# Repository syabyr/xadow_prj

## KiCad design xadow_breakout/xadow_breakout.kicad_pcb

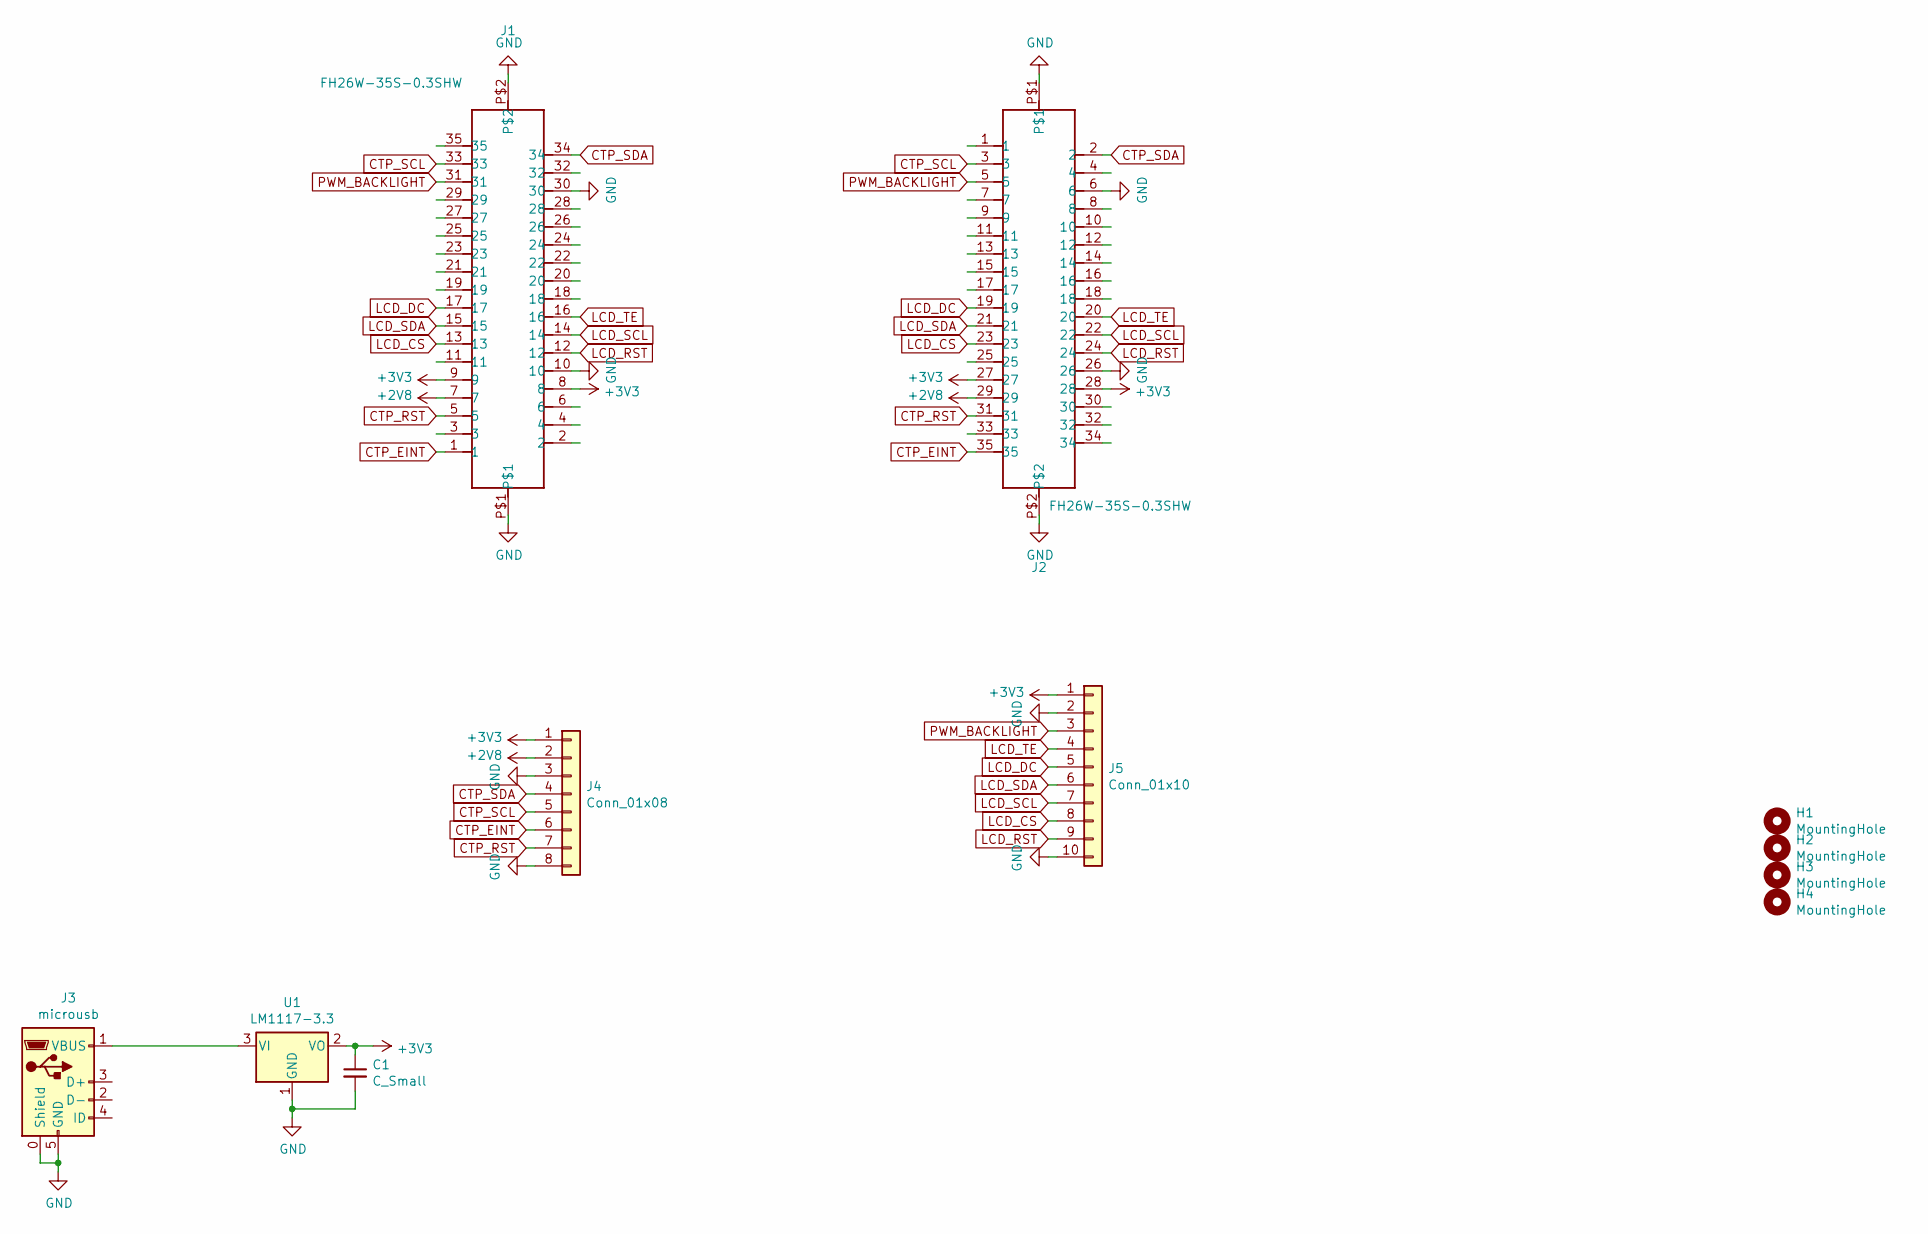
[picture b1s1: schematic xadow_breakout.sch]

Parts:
C1: C_Small; C_1210_3225Metric_Pad1.33x2.70mm_HandSolder
H1, H2, H3, H4: MountingHole; MountingHole_3.2mm_M3_ISO7380
J1, J2: FH26W-35S-0.3SHW; FPC35-SMD-0.3(FH26W)
J3: microusb; USB_Micro-B_Wuerth_629105150521_CircularHoles
J4: Conn_01x08; PinHeader_1x08_P2.54mm_Vertical
J5: Conn_01x10; PinHeader_1x10_P2.54mm_Vertical
U1: LM1117-3.3; SOT-223-3_TabPin2

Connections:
+2V8: J1.7, J2.29, J4.2
+3V3: C1.1, J1.8, J1.9, J2.27, J2.28, J4.1, J5.1, U1.2 (VO)
CTP_EINT: J1.1, J2.35, J4.6
CTP_RST: J1.5, J2.31, J4.7
CTP_SCL: J1.33, J2.3, J4.5
CTP_SDA: J1.34, J2.2, J4.4
GND: C1.2, J1.10, J1.30, J1.P$1, J1.P$2, J2.6, J2.26, J2.P$1, J2.P$2, J3.0 (Shield), J3.5 (GND), J4.3, J4.8, J5.2, J5.10, U1.1 (GND)
LCD_CS: J1.13, J2.23, J5.8
LCD_DC: J1.17, J2.19, J5.5
LCD_RST: J1.12, J2.24, J5.9
LCD_SCL: J1.14, J2.22, J5.7
LCD_SDA: J1.15, J2.21, J5.6
LCD_TE: J1.16, J2.20, J5.4
unnamed: J3.1 (VBUS), U1.3 (VI)
PWM_BACKLIGHT: J1.31, J2.5, J5.3

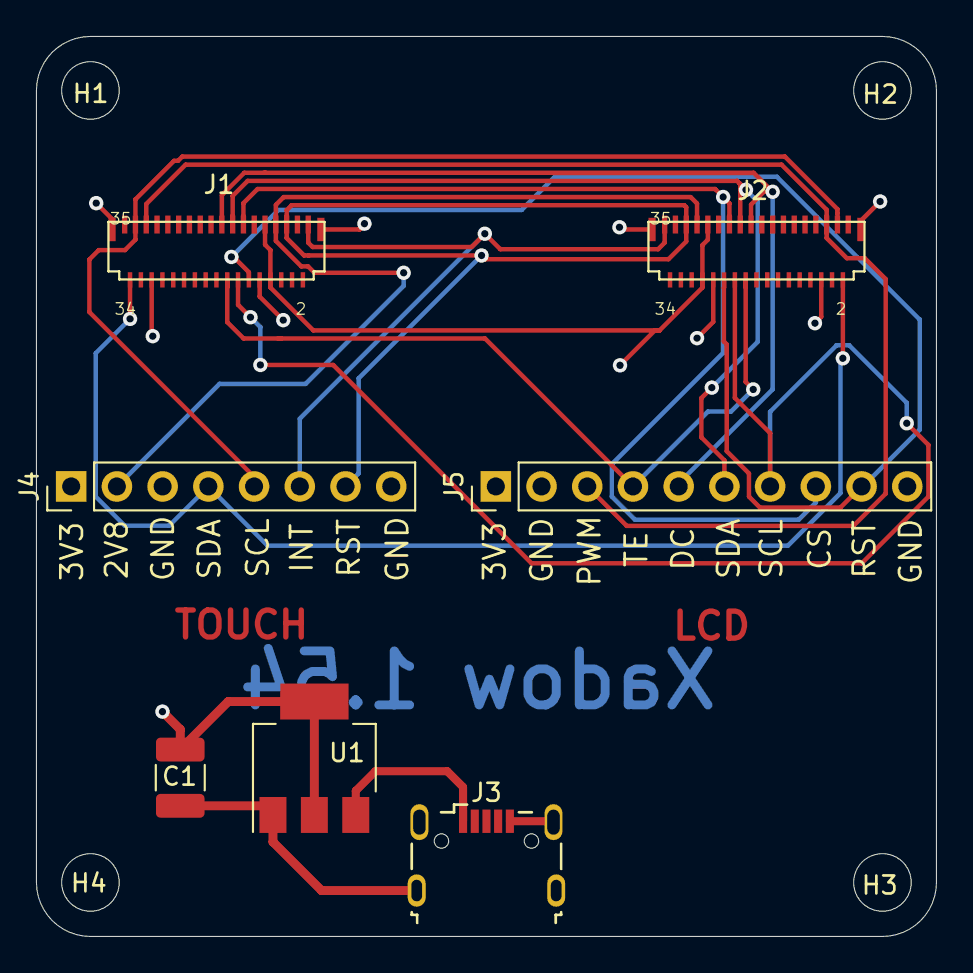
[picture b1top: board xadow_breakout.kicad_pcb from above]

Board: 4 copper layers, 50.0 x 50.0 mm, 11 parts (0 on the bottom side), 15 nets.

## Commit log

2022-01-18 breakout
2022-01-20 20220120
2022-01-20 xadow
